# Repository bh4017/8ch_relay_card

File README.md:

# 8ch_relay_card
An 8 channel relay card for converting digital IO into high current switched outputs

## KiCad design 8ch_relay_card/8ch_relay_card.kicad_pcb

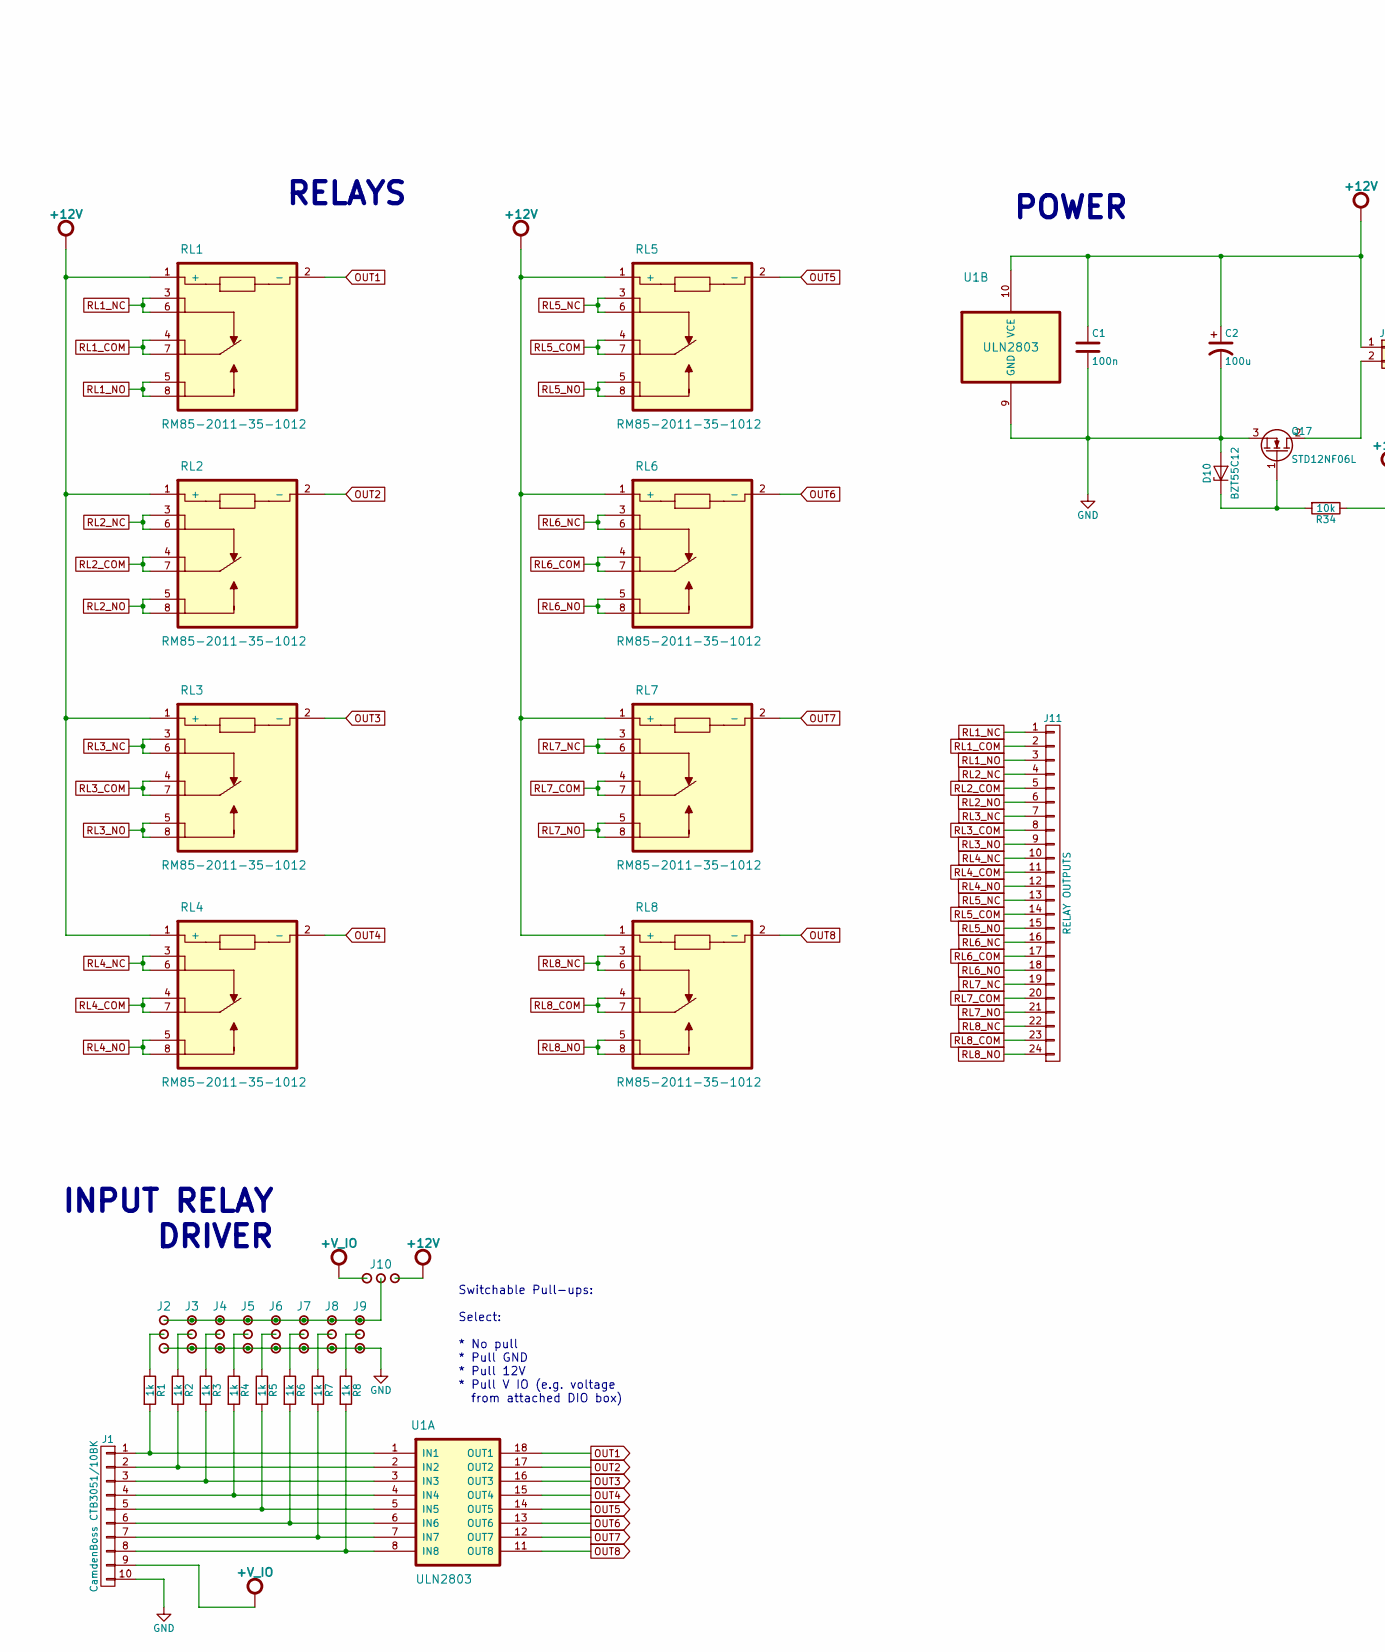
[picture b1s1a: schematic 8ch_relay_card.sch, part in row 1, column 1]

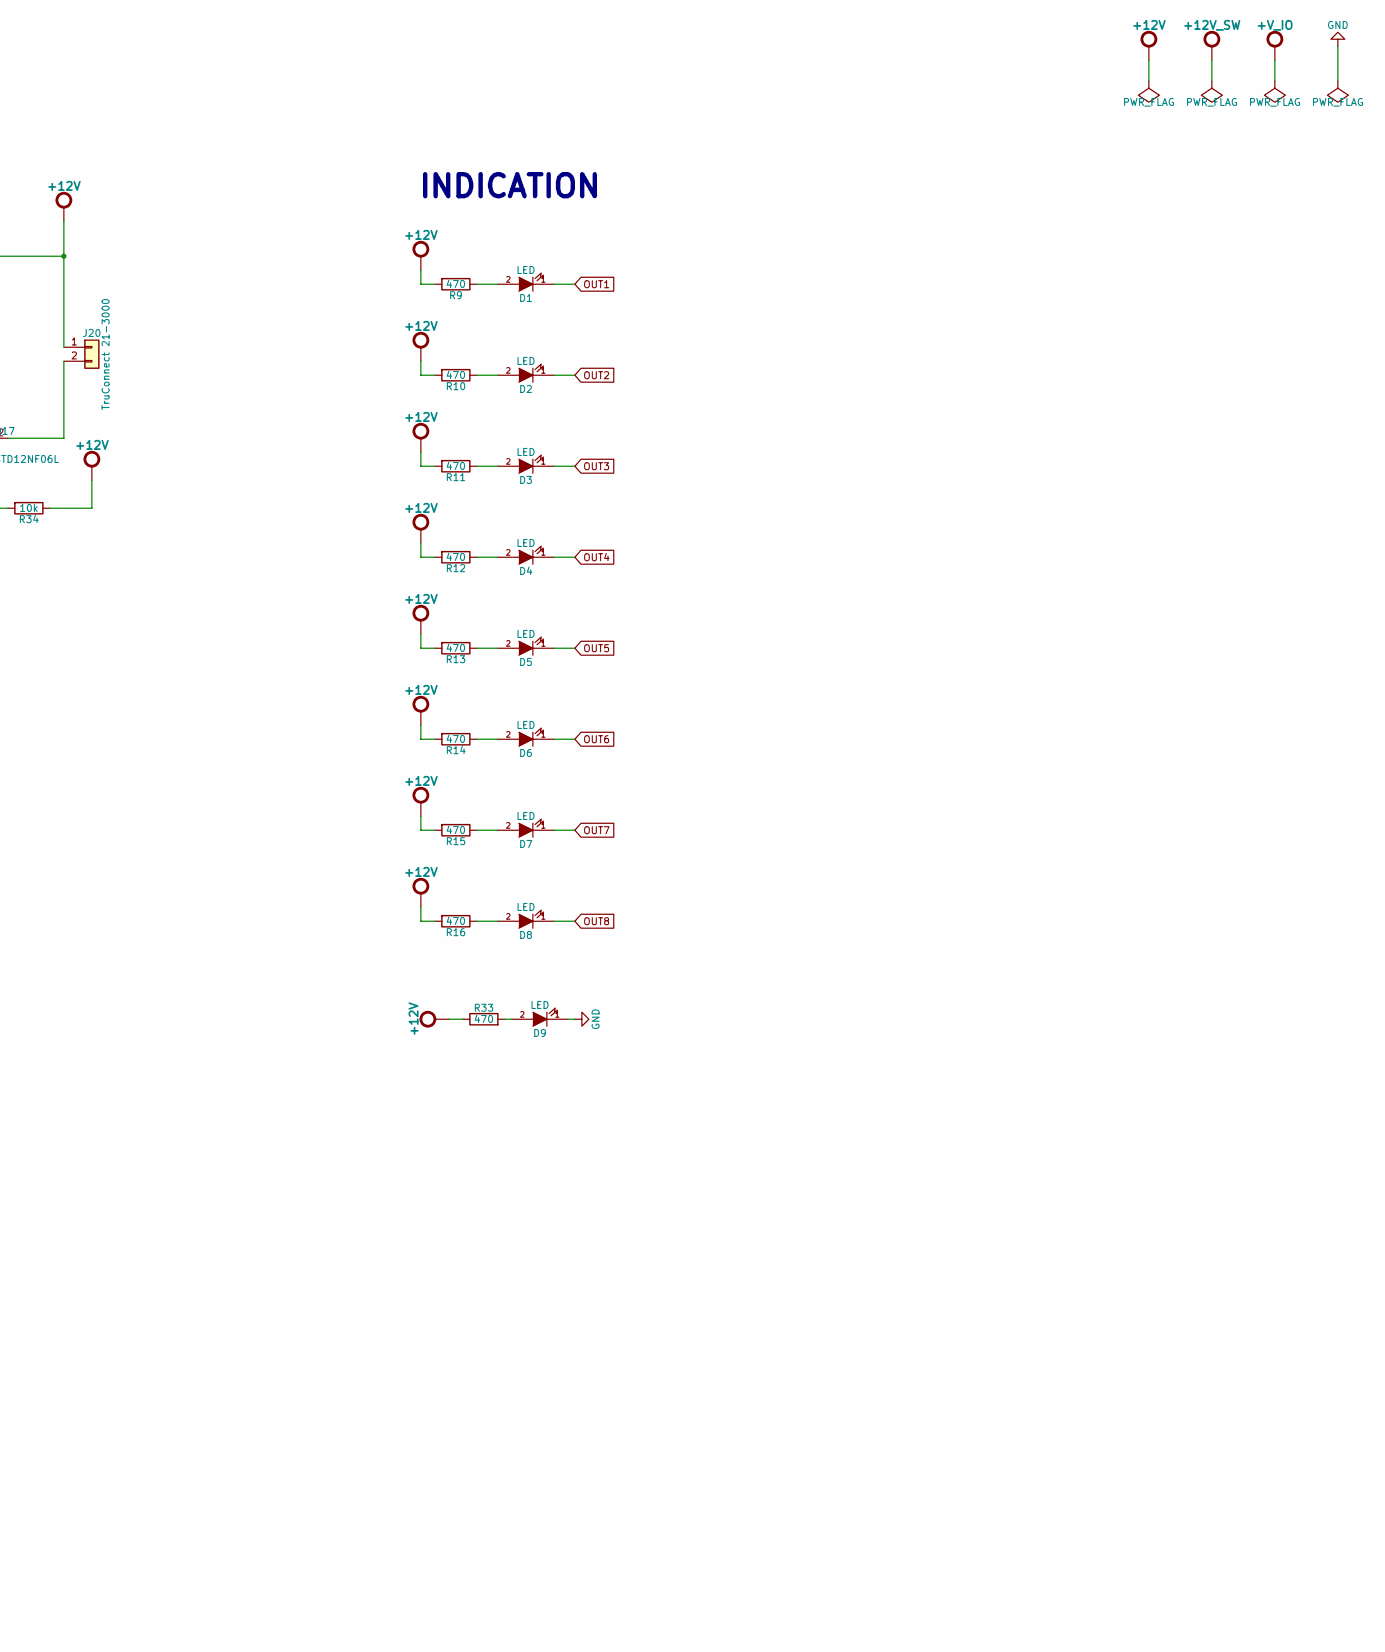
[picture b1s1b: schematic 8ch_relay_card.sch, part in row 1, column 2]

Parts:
C1: 100n; C_0805_HandSoldering
C2: 100u; c_elec_8x10.5
D1, D2, D3, D4, D5, D6, D7, D8, D9: LED; LED-5MM
D10: BZT55C12; BZT55
J1: CamdenBoss CTB3051/10BK; CamdenBossCTB3051_10BK
J2, J3, J4, J5, J6, J7, J8, J9, J10: jmp_3way; HEAD-1row-2.54mm-3way
J11: RELAY OUTPUTS; TruConnect_21-1812_x8_stacked
J20: TruConnect 21-3000; TruConnect_21-3000
Q17: STD12NF06L; DPAK_DGS
R1, R2, R3, R4, R5, R6, R7, R8: 1k; R_0805
R9, R10, R11, R12, R13, R14, R15, R16, R33: 470; R_0805
R34: 10k; R_0805
RL1, RL2, RL3, RL4, RL5, RL6, RL7, RL8: RM85-2011-35-1012
U1: ULN2803; DIP-18_W7.62mm

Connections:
+12V: C1.1, C2.1, J10.1, J20.1, R9.2, R10.2, R11.2, R12.2, R13.2, R14.2, R15.2, R16.2, R33.1, R34.1, RL1.1 (+), RL2.1 (+), RL3.1 (+), RL4.1 (+), RL5.1 (+), RL6.1 (+), RL7.1 (+), RL8.1 (+), U1.10 (VCE)
+V_IO: J1.9, J10.3
GND: C1.2, C2.2, D9.1 (K), D10.2 (A), J1.10, J2.3, J3.3, J4.3, J5.3, J6.3, J7.3, J8.3, J9.3, Q17.3 (S), U1.9 (GND)
unnamed: D1.2 (A), R9.1
unnamed: D2.2 (A), R10.1
unnamed: D3.2 (A), R11.1
unnamed: D4.2 (A), R12.1
unnamed: D5.2 (A), R13.1
unnamed: D6.2 (A), R14.1
unnamed: D7.2 (A), R15.1
unnamed: D8.2 (A), R16.1
unnamed: D9.2 (A), R33.2
unnamed: D10.1 (K), Q17.1 (G), R34.2
unnamed: J1.1, R1.2, U1.1 (IN1)
unnamed: J1.2, R2.2, U1.2 (IN2)
unnamed: J1.3, R3.2, U1.3 (IN3)
unnamed: J1.4, R4.2, U1.4 (IN4)
unnamed: J1.5, R5.2, U1.5 (IN5)
unnamed: J1.6, R6.2, U1.6 (IN6)
unnamed: J1.7, R7.2, U1.7 (IN7)
unnamed: J1.8, R8.2, U1.8 (IN8)
unnamed: J2.2, R1.1
unnamed: J3.2, R2.1
unnamed: J4.2, R3.1
unnamed: J5.2, R4.1
unnamed: J6.2, R5.1
unnamed: J7.2, R6.1
unnamed: J8.2, R7.1
unnamed: J9.2, R8.1
unnamed: J2.1, J3.1, J4.1, J5.1, J6.1, J7.1, J8.1, J9.1, J10.2
unnamed: J20.2, Q17.2 (D)
OUT1: D1.1 (K), RL1.2 (-), U1.18 (OUT1)
OUT2: D2.1 (K), RL2.2 (-), U1.17 (OUT2)
OUT3: D3.1 (K), RL3.2 (-), U1.16 (OUT3)
OUT4: D4.1 (K), RL4.2 (-), U1.15 (OUT4)
OUT5: D5.1 (K), RL5.2 (-), U1.14 (OUT5)
OUT6: D6.1 (K), RL6.2 (-), U1.13 (OUT6)
OUT7: D7.1 (K), RL7.2 (-), U1.12 (OUT7)
OUT8: D8.1 (K), RL8.2 (-), U1.11 (OUT8)
RL1_COM: J11.2, RL1.4, RL1.7
RL1_NC: J11.1, RL1.3, RL1.6
RL1_NO: J11.3, RL1.5, RL1.8
RL2_COM: J11.5, RL2.4, RL2.7
RL2_NC: J11.4, RL2.3, RL2.6
RL2_NO: J11.6, RL2.5, RL2.8
RL3_COM: J11.8, RL3.4, RL3.7
RL3_NC: J11.7, RL3.3, RL3.6
RL3_NO: J11.9, RL3.5, RL3.8
RL4_COM: J11.11, RL4.4, RL4.7
RL4_NC: J11.10, RL4.3, RL4.6
RL4_NO: J11.12, RL4.5, RL4.8
RL5_COM: J11.14, RL5.4, RL5.7
RL5_NC: J11.13, RL5.3, RL5.6
RL5_NO: J11.15, RL5.5, RL5.8
RL6_COM: J11.17, RL6.4, RL6.7
RL6_NC: J11.16, RL6.3, RL6.6
RL6_NO: J11.18, RL6.5, RL6.8
RL7_COM: J11.20, RL7.4, RL7.7
RL7_NC: J11.19, RL7.3, RL7.6
RL7_NO: J11.21, RL7.5, RL7.8
RL8_COM: J11.23, RL8.4, RL8.7
RL8_NC: J11.22, RL8.3, RL8.6
RL8_NO: J11.24, RL8.5, RL8.8

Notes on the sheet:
Switchable Pull-ups: Select: * No pull * Pull GND * Pull 12V * Pull V IO (e.g. voltage from attached DIO box)
RELAYS
INPUT RELAY DRIVER
POWER
INDICATION

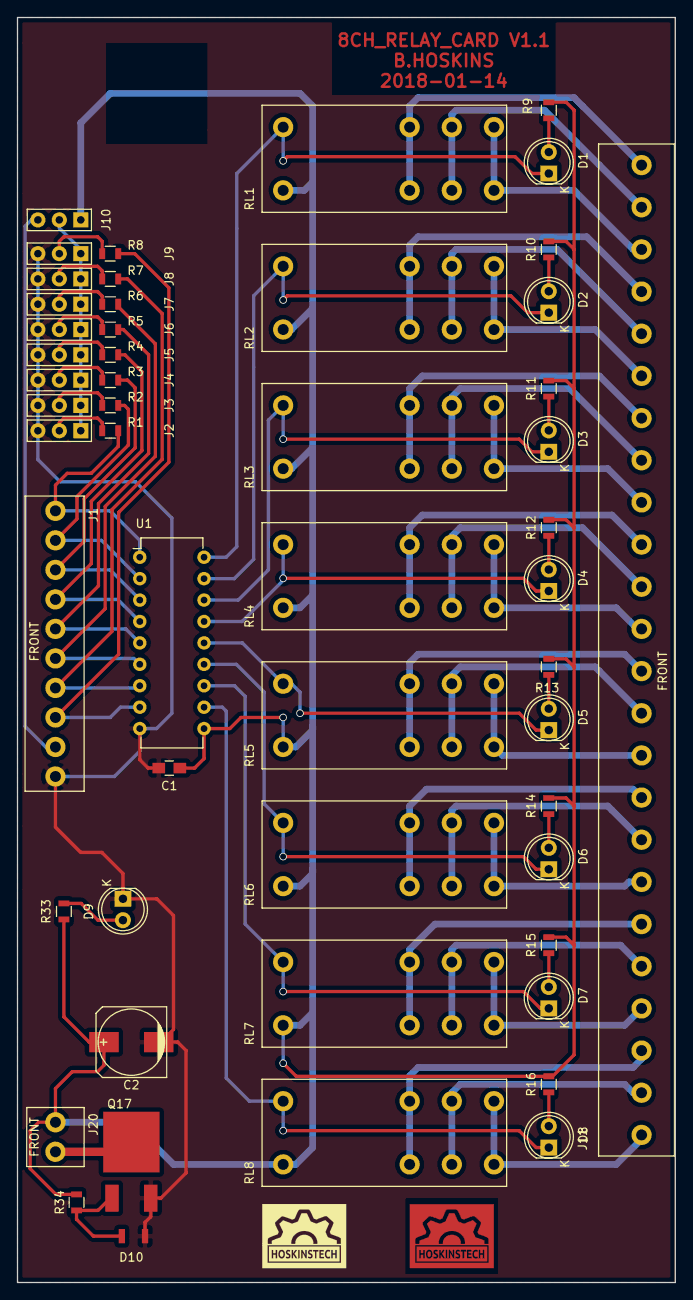
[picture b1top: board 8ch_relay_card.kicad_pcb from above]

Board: 2 copper layers, 78.0 x 150.0 mm, 52 parts (0 on the bottom side), 63 nets.

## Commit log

2017-11-02 still working on the schematic
2017-11-02 More work on the schematic
2017-11-03 First revision of schematic completed
2017-11-05 scheamtic finished, PCB almost done
2017-11-05 Removed bi-colour LEDs and reverted to single colour LEDs. PCB Design finished.
2018-01-14 V1.1: Changed relay layout to improve solderability, especially on home-made PCBs without through-plating. Changed output connector to a all-in-one stacked version
